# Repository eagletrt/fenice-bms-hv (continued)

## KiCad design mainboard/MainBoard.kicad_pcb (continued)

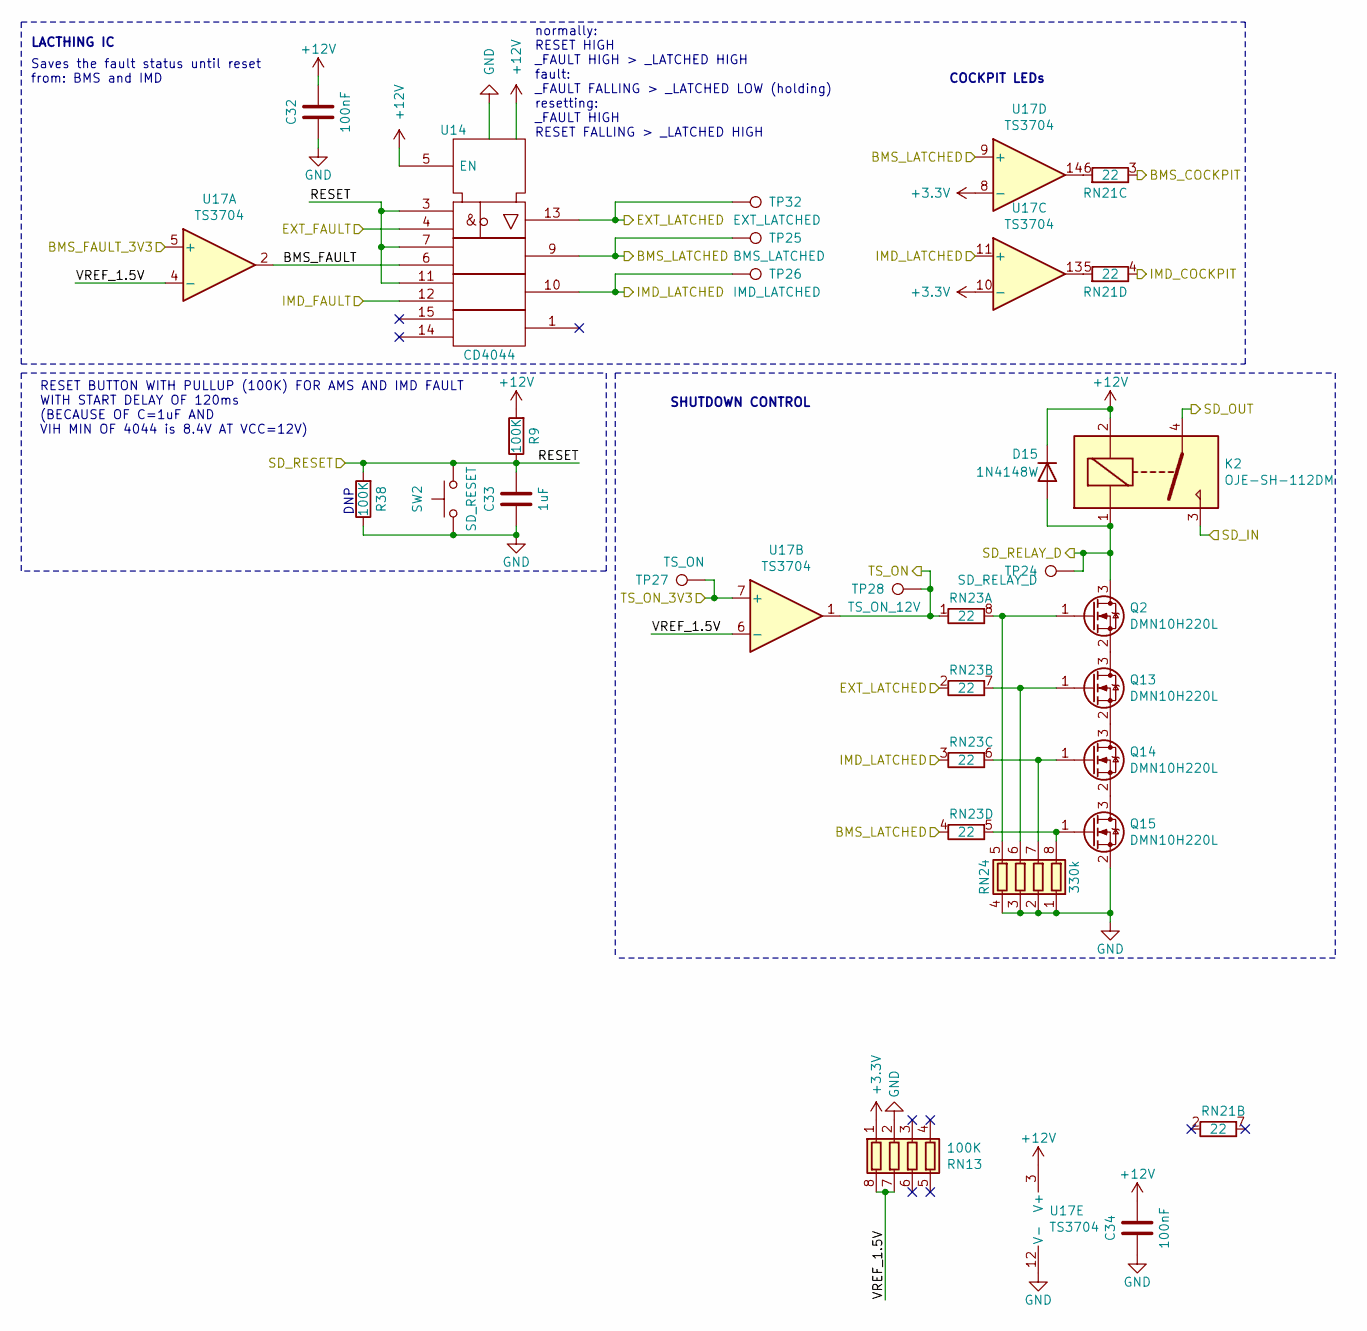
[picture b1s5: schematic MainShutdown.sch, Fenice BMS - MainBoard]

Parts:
C32, C34: 100nF; C_0603_1608Metric
C33: 1uF; C_0805_2012Metric
D15: 1N4148W; D_SOD-123
K2: OJE-SH-112DM
Q2, Q13, Q14, Q15: DMN10H220L; SOT-23
R9, R38: 100K; R_0603_1608Metric
RN13: 100K; R_Array_Convex_4x0603
RN21, RN23: 22; R_Array_Convex_4x0603
RN24: 330k; R_Array_Convex_4x0603
SW2: SD_RESET; SW_SPST_FSMSM
TP24: SD_RELAY_D; TestPoint_Pad_D1.0mm
TP25: BMS_LATCHED; TestPoint_Pad_D1.0mm
TP26: IMD_LATCHED; TestPoint_Pad_D1.0mm
TP27: TS_ON; TestPoint_Pad_D1.0mm
TP28: TS_ON_12V; TestPoint_Pad_D1.0mm
TP32: EXT_LATCHED; TestPoint_Pad_D1.0mm
U14: CD4044; TSSOP-16_4.4x5mm_P0.65mm
U17: TS3704; TSSOP-14_4.4x5mm_P0.65mm

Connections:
+12V: C32.1, C34.1, D15.1 (K), K2.2, R9.2, U14.5 (EN), U14.16 (Vdd), U17.3 (V+); also elsewhere on the board
/BMS_COCKPIT: RN21.3 (R3.1); also elsewhere on the board
/EXT_FAULT: U14.4; also elsewhere on the board
/IMD_COCKPIT: RN21.4 (R4.1); also elsewhere on the board
/IMD_FAULT: U14.12; also elsewhere on the board
/MCU/BMS_FAULT: U17.5 (+); also elsewhere on the board
/MCU/TS_ON: TP27.1, U17.7 (+); also elsewhere on the board
/Probing/BMS_LATCHED: RN23.4 (R4.1), TP25.1, U14.9, U17.9 (+); also elsewhere on the board
/Probing/EXT_LATCHED: RN23.2 (R2.1), TP32.1, U14.13; also elsewhere on the board
/Probing/IMD_LATCHED: RN23.3 (R3.1), TP26.1, U14.10, U17.11 (+); also elsewhere on the board
/Probing/SD_RELAY_D: D15.2 (A), K2.1, Q2.3 (D), TP24.1; also elsewhere on the board
/Probing/TS_ON: RN23.1 (R1.1), TP28.1, U17.1; also elsewhere on the board
/SD_IN: K2.3; also elsewhere on the board
/SD_OUT: K2.4; also elsewhere on the board
/SD_RESET: C33.1, R9.1, R38.2, SW2.1, U14.3, U14.7, U14.11; also elsewhere on the board
/Shutdown/BMS_FAULT: U14.6, U17.2
/Shutdown/VREF_1.5V: RN13.7 (R2.2), RN13.8 (R1.2), U17.4 (-), U17.6 (-)
GND: C32.2, C33.2, C34.2, Q15.2 (S), R38.1, RN13.2 (R2.1), RN24.1 (R1.1), RN24.2 (R2.1), RN24.3 (R3.1), RN24.4 (R4.1), SW2.2, U14.8 (Vss), U17.12 (V-); also elsewhere on the board
unnamed: Q2.1 (G), RN23.8 (R1.2), RN24.5 (R4.2)
unnamed: Q13.1 (G), RN23.7 (R2.2), RN24.6 (R3.2)
unnamed: Q13.2 (S), Q14.3 (D)
unnamed: Q2.2 (S), Q13.3 (D)
unnamed: Q14.1 (G), RN23.6 (R3.2), RN24.7 (R2.2)
unnamed: Q14.2 (S), Q15.3 (D)
unnamed: Q15.1 (G), RN23.5 (R4.2), RN24.8 (R1.2)
unnamed: RN21.5 (R4.2), U17.13
unnamed: RN21.6 (R3.2), U17.14

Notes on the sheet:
SHUTDOWN CONTROL
RESET BUTTON WITH PULLUP (100K) FOR AMS AND IMD FAULT WITH START DELAY OF 120ms (BECAUSE OF C=1uF AND VIH MIN OF 4044 is 8.4V AT VCC=12V)
LACTHING IC
Saves the fault status until reset from: BMS and IMD
normally: RESET HIGH _FAULT HIGH > _LATCHED HIGH fault: _FAULT FALLING > _LATCHED LOW (holding) resetting: _FAULT HIGH RESET FALLING > _LATCHED HIGH
DNP
COCKPIT LEDs

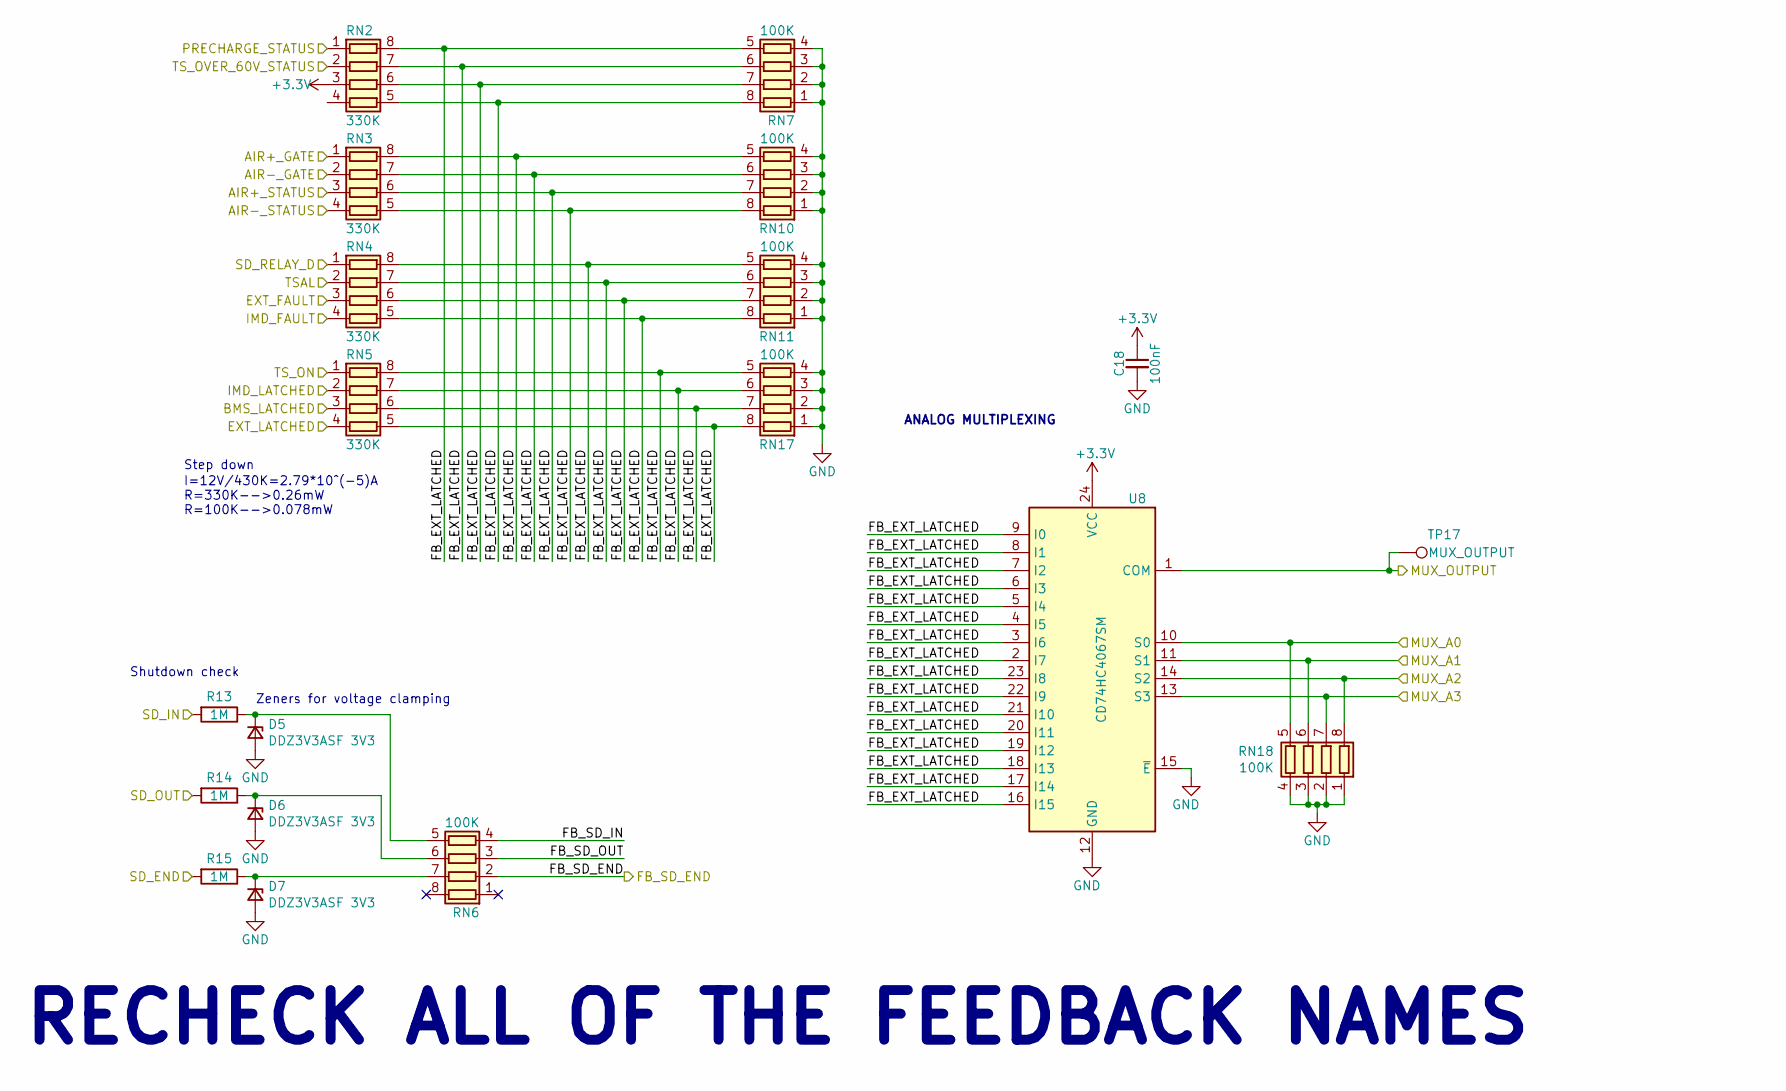
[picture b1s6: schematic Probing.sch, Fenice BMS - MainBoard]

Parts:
C18: 100nF; C_0603_1608Metric
D5, D6, D7: DDZ3V3ASF 3V3; D_SOD-323
R13, R14, R15: 1M; R_0603_1608Metric
RN2, RN3, RN4, RN5: 330K; R_Array_Convex_4x0603
RN6, RN7, RN10, RN11, RN17, RN18: 100K; R_Array_Convex_4x0603
TP17: MUX_OUTPUT; TestPoint_Pad_D1.0mm
U8: CD74HC4067SM; TSSOP-24_4.4x7.8mm_P0.65mm

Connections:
/AIRs/AIR+_GATE: RN3.1 (R1.1); also elsewhere on the board
/AIRs/AIR+_STATUS: RN3.3 (R3.1); also elsewhere on the board
/AIRs/AIR-_GATE: RN3.2 (R2.1); also elsewhere on the board
/AIRs/AIR-_STATUS: RN3.4 (R4.1); also elsewhere on the board
/EXT_FAULT: RN4.3 (R3.1); also elsewhere on the board
/HV/PRECHARGE_STATUS: RN2.1 (R1.1); also elsewhere on the board
/HV/TS_OVER_60V_STATUS: RN2.2 (R2.1); also elsewhere on the board
/IMD_FAULT: RN4.4 (R4.1); also elsewhere on the board
/MCU/FB_SD_END: RN6.2 (R2.1); also elsewhere on the board
/MCU/MUX_A0: RN18.5 (R4.2), U8.10 (S0)
/MCU/MUX_A1: RN18.6 (R3.2), U8.11 (S1)
/MCU/MUX_A2: RN18.8 (R1.2), U8.14 (S2)
/MCU/MUX_A3: RN18.7 (R2.2), U8.13 (S3)
/MCU/MUX_OUTPUT: TP17.1, U8.1 (COM); also elsewhere on the board
/Probing/BMS_LATCHED: RN5.3 (R3.1); also elsewhere on the board
/Probing/EXT_LATCHED: RN5.4 (R4.1); also elsewhere on the board
/Probing/FB_EXT_LATCHED: RN2.5 (R4.2), RN2.6 (R3.2), RN2.7 (R2.2), RN2.8 (R1.2), RN3.5 (R4.2), RN3.6 (R3.2), RN3.7 (R2.2), RN3.8 (R1.2), RN4.5 (R4.2), RN4.6 (R3.2), RN4.7 (R2.2), RN4.8 (R1.2), RN5.5 (R4.2), RN5.6 (R3.2), RN5.7 (R2.2), RN5.8 (R1.2), RN7.5 (R4.2), RN7.6 (R3.2), RN7.7 (R2.2), RN7.8 (R1.2), RN10.5 (R4.2), RN10.6 (R3.2), RN10.7 (R2.2), RN10.8 (R1.2), RN11.5 (R4.2), RN11.6 (R3.2), RN11.7 (R2.2), RN11.8 (R1.2), RN17.5 (R4.2), RN17.6 (R3.2), RN17.7 (R2.2), RN17.8 (R1.2), U8.2 (I7), U8.3 (I6), U8.4 (I5), U8.5 (I4), U8.6 (I3), U8.7 (I2), U8.8 (I1), U8.9 (I0), U8.16 (I15), U8.17 (I14), U8.18 (I13), U8.19 (I12), U8.20 (I11), U8.21 (I10), U8.22 (I9), U8.23 (I8)
/Probing/FB_SD_IN: RN6.4 (R4.1)
/Probing/FB_SD_OUT: RN6.3 (R3.1)
/Probing/IMD_LATCHED: RN5.2 (R2.1); also elsewhere on the board
/Probing/SD_RELAY_D: RN4.1 (R1.1); also elsewhere on the board
/Probing/TS_ON: RN5.1 (R1.1); also elsewhere on the board
/SD_END: R15.2; also elsewhere on the board
/SD_IN: R13.2; also elsewhere on the board
/SD_OUT: R14.2; also elsewhere on the board
/TSAL: RN4.2 (R2.1); also elsewhere on the board
GND: C18.2, D5.2 (A), D6.2 (A), D7.2 (A), RN7.1 (R1.1), RN7.2 (R2.1), RN7.3 (R3.1), RN7.4 (R4.1), RN10.1 (R1.1), RN10.2 (R2.1), RN10.3 (R3.1), RN10.4 (R4.1), RN11.1 (R1.1), RN11.2 (R2.1), RN11.3 (R3.1), RN11.4 (R4.1), RN17.1 (R1.1), RN17.2 (R2.1), RN17.3 (R3.1), RN17.4 (R4.1), RN18.1 (R1.1), RN18.2 (R2.1), RN18.3 (R3.1), RN18.4 (R4.1), U8.12 (GND), U8.15 (~E); also elsewhere on the board
unnamed: D5.1 (K), R13.1, RN6.5 (R4.2)
unnamed: D6.1 (K), R14.1, RN6.6 (R3.2)
unnamed: D7.1 (K), R15.1, RN6.7 (R2.2)

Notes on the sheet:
I=12V/430K=2.79*10^(-5)A R=330K-->0.26mW R=100K-->0.078mW
Step down
Zeners for voltage clamping
ANALOG MULTIPLEXING
RECHECK ALL OF THE FEEDBACK NAMES
Shutdown check

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
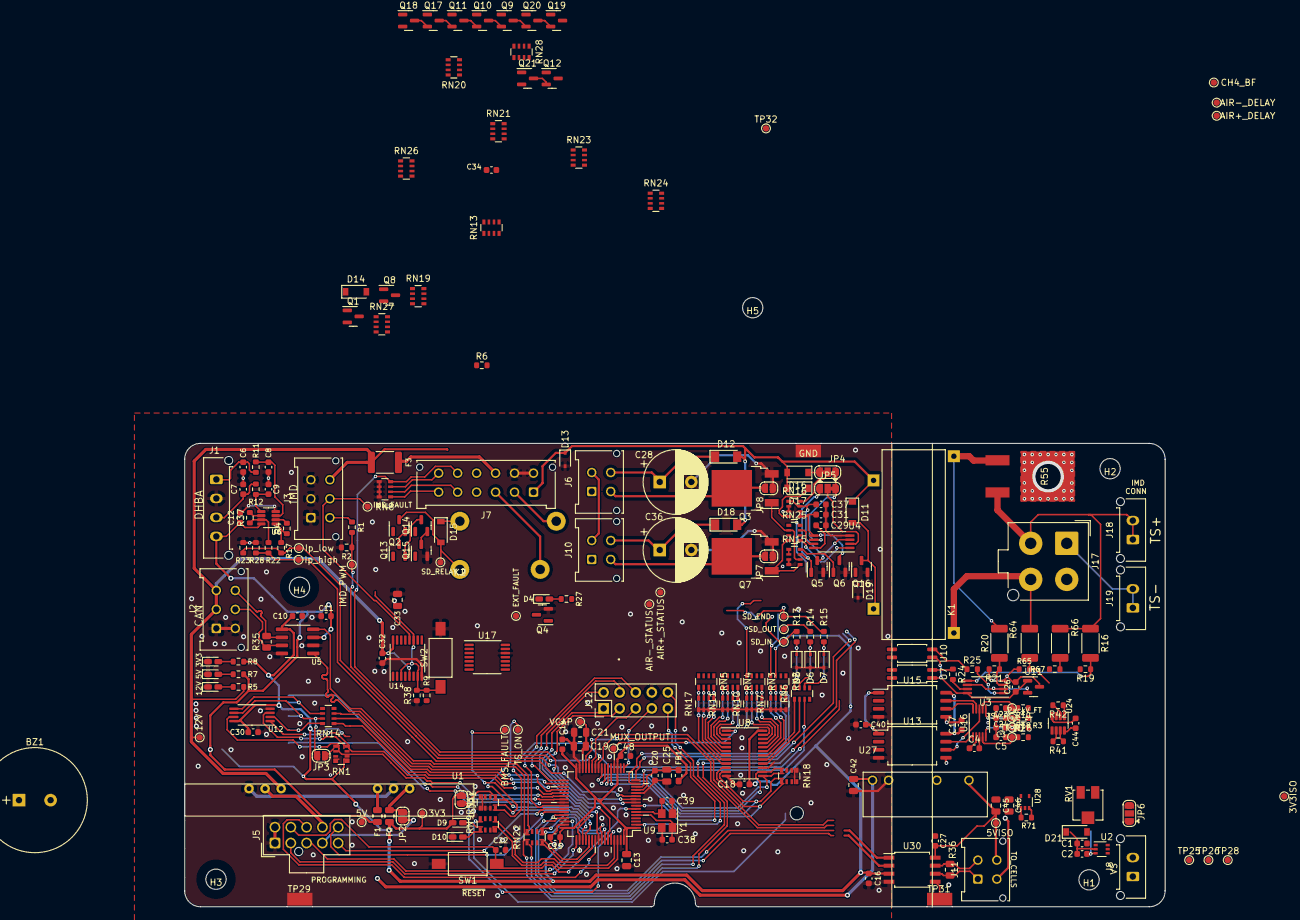
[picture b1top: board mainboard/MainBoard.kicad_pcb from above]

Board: 2 copper layers, 155.0 x 73.2 mm, 246 parts (1 on the bottom side), 199 nets.

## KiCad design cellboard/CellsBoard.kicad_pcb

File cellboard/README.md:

# CELLBOARD
Formula SAE - unitn

## Authors
Latest first:  
- Francesco Osti v2.1.4  
- Franco Tabarelli v2.0 - 2.1.3  
- Gregor Gombač v0 -   

## Version 2.1.4
Compared to last version we now use NTC termistor to monitor temperature and no longer use digital temperature sensors mounted on flexible PCB

## Project structure
```
cellboard
|-- CellsBoard.pro                    # Project file
|-- CellsBoard.sch                    # Cellboard main schematic
|-- PowerSupply.sch                   # Power sources schematic
|-- Balance.sch                       # Balancer schematic
|-- temperatureADC.sch                # Temperature measurement schematic
|-- Temperature section.sch           # STM microcontroller schematic
|-- LTC6813-1.sch                     # Cell voltage monitor IC schematic
|-- CellsBoard.kicad_pcb              # PCB
|-- CellsBoard-cache.lib              # Local cache of symbols        
|-- CellsBoard.net                    # Netlist
|-- CellsBoard-rescue.dcm             # Component library stuff
|-- CellsBoard-rescue.lib             # Component library stuff
|-- fp-info-cache                     # Cache of footprints
|-- fp-lib-table                      # List of footprint lib files
|-- sym-lib-table                     # List of symbols lib files
|-- modules/                          # Local symbol library files
|   |-- CellsBoard.pretty/            # Local footprint library files
|   |-- logo.kicad_mod/               # Logos fotprints
|   |-- packages3d/                   # 3D models
|   |-- simbolo_E-Agle.pretty/        # Logos E-Agle fotprints
|   |-- simbolo HV/                   # Logos HV fotprints
|-- gerber/                           # Gerber outputs
|-- library/                          # Local symbol library files
```

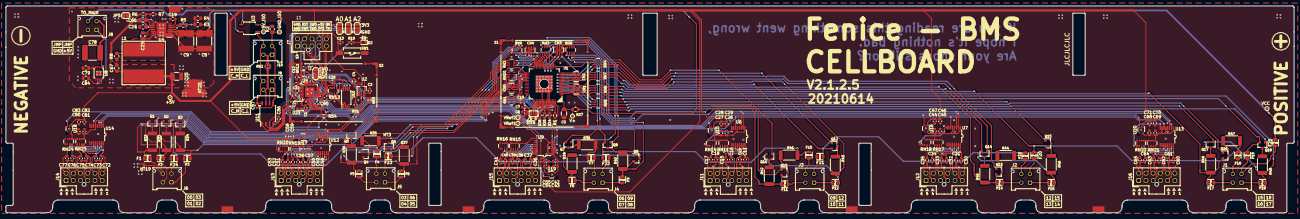
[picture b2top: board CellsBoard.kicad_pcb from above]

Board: 2 copper layers, 445.5 x 71.5 mm, 275 parts (0 on the bottom side), 245 nets.

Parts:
C1, C11, C13, C14, C15, C16, C17, C18, C20, C21, C22, C26, C28, C30, C31, C32, C33, C34, C35, C36, C37, C38, C39, C40, C41, C42, C45, C47, C48, C49, C50, C51, C52, C53, C54, C57, C59, C60, C61, C62, C63, C64, C65, C69, C71, C72, C73, C74, C75, C76, C77, C81, C83, C85, C86, C87: 100nF; C_0603_1608Metric
C2, C3, C4, C6, C7, C10, C12, C27, C29, C43, C44, C46, C55, C56, C58, C68, C70, C80, C82: 1uF; C_0603_1608Metric
C5: 100nF_HV; C_1206_3216Metric
C8, C9, C78: 1u_HV; C_2220_5650Metric_Pad1.97x5.40mm_HandSolder
C19: 22n; C_0603_1608Metric_Pad1.08x0.95mm_HandSolder
C23, C66: 10n; C_0805_2012Metric_Pad1.18x1.45mm_HandSolder
C24: 1u; C_0805_2012Metric_Pad1.18x1.45mm_HandSolder
C25: 47u; C_1210_3225Metric_Pad1.33x2.70mm_HandSolder
C67: 3n; C_0805_2012Metric_Pad1.18x1.45mm_HandSolder
C79: 100n; C_0805_2012Metric
C84: 10n; C_0805_2012Metric
CN1, CN2, CN3, CN4, CN5: 10nF_array; C_4Array_1206
D2: LED_Small; D_0603_1608Metric
F1, F2, F3, F4, F5, F6, F7, F8, F9, F10, F11, F12, F13, F14, F15, F16, F17, F18, F19, F20, F21, F22, F23, F24, F25: Fuse; Fuse_0805
J1, J2, J3, J4, J5, J6: Conn_02x02_Odd_Even; Molex_Micro-Fit_3.0_43045-0412_2x02_P3.00mm_Vertical
J7: Conn_02x05_Top_Bottom; Molex_Nano-Fit_105310-xx10_2x05_P2.50mm_Vertical
J8: Conn_02x02_Counter_Clockwise; Molex_Micro-Fit_3.0_43045-0412_2x02_P3.00mm_Vertical
J9, J10: BUS; Molex_Micro-Fit_3.0_43045-0412_2x02_P3.00mm_Vertical
J11, J12, J13, J14, J15, J16: Conn_02x06_Top_Bottom; Molex_Nano-Fit_105310-xx12_2x06_P2.50mm_Vertical
JP1, JP2, JP3, JP4: SolderJumper_3_Open; SolderJumper-3_P1.3mm_Open_RoundedPad1.0x1.5mm
JP5: SolderJumper_2_Open; SolderJumper-2_P1.3mm_Open_RoundedPad1.0x1.5mm
JP20: DTEN; Jumper_adafruit
L1: 56u; sdr1307
NT0, NT1, NT2, NT3, NT4, NT5, NT6, NT7, NT8, NT9, NT10, NT11, NT12, NT13, NT14, NT15, NT16, NT17, NT18, NT19: Net-Tie_2; NetTie-2_SMD_Pad0.5mm
NT20: Net-Tie_2; NetTie-2_SMD_Pad2.0mm
Q1, Q2, Q3, Q4, Q5, Q6, Q7, Q8, Q9, Q10, Q11, Q12, Q13, Q14: TSM3401CX RFG; SOT-23
Q15, Q16, Q17, Q18: BSS308PE; SOT-23
R1: 100; R_0603_1608Metric
R2: 1.24k; R_0805_2012Metric_Pad1.20x1.40mm_HandSolder
R3: 100k; R_0805_2012Metric_Pad1.20x1.40mm_HandSolder
R4: 2k; R_0805_2012Metric_Pad1.20x1.40mm_HandSolder
R5: 215k; R_0805_2012Metric_Pad1.20x1.40mm_HandSolder
R6: 3k; R_0603_1608Metric_Pad0.98x0.95mm_HandSolder
R7: 2k; R_0603_1608Metric_Pad0.98x0.95mm_HandSolder
R8: 255k; R_0805_2012Metric_Pad1.20x1.40mm_HandSolder
R19: 3K3; R_0603_1608Metric
R24, R25: 1k; R_0603_1608Metric
R26: 1M; R_0603_1608Metric
R27: 100; R_0805_2012Metric
R32, R33, R34, R35, R36, R37, R38, R39, R40, R41, R42, R43, R44, R45, R46, R47, R48, R49: Rdsc; R_2512_6332Metric
R51: 1K; R_0603_1608Metric
R52: 150; R_0603_1608Metric
R53: 5K; R_0603_1608Metric
R54: 10K; R_0603_1608Metric
RN1, RN2, RN3, RN4, RN5: 3K3; R_Array_Convex_4x0603
RN6, RN7, RN8, RN9, RN10: 39; R_Array_Convex_4x0603
RN11, RN14, RN15, RN16, RN17, RN18, RN19, RN20, RN21, RN22, RN23, RN24: x; R_Array_Convex_4x0603
RN12: 1K; R_Array_Convex_2x0603
RN13: 1K; R_Array_Convex_4x0603
S1: RF_Shield_One_Piece; Harwin_shield_30x30mm_right_angle_clips
S2: RF_Shield_One_Piece; Harwin_shield_20x30mm_only_right_angle_clips
SW1: RESET; Button_SMD_6x3.5x4.3mm
TP1, TP2, TP3, TP4, TP7: TestPoint; TestPoint_GNDedge_toponly
TP5: VRef1; TestPoint_Pad_D1.0mm
TP6: VRef2; TestPoint_Pad_D1.0mm
TP8: V+; TestPoint_Pad_D1.0mm
TP9: +5V; TestPoint_Pad_D1.0mm
TP10: 5V_ISO; TestPoint_Pad_D1.0mm
TP11: GND_ISO; TestPoint_Pad_D1.0mm
TP12: VCC; TestPoint_Pad_D1.0mm
U1: LTC6813-1; LTC6813-1_minimal
U2: MCP1812; SOT-23_Handsoldering
U3: CPC1125N; SOP-4_3.8x4.1mm_P2.54mm
U4: LM5161PWP; HTSSOP-14-1EP_4.4x5mm_P0.65mm_EP3.4x5mm_Mask3x3.1mm
U5: STM32L432KBUx; QFN-32-1EP_5x5mm_P0.5mm_EP3.45x3.45mm
U6, U7, U9, U12, U13, U14: ADC128D818; TSSOP-16_4.4x5mm_P0.65mm
U8: MAQ5281; MSOP-8-1EP_3x3mm_P0.65mm_EP1.68x1.88mm
U10: M95256-W; TSSOP-8_4.4x3mm_P0.65mm
U11: MAX14878AWA+; SOIC-8_5.23x5.23mm_P1.27mm
U15, U16, U17, U18, U19, U20: MCP1811AT-033LT; SOT-353_SC-70-5
U21: DSC61XX; 4-Lead_CDFN_2.5x2.0mm

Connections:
+3V3: C1.2, C2.1, C4.1, C12.1, C20.2, C21.1, C22.1, C85.1, C86.2, J7.4, JP1.3, JP3.3, JP4.3, R51.2, R53.1, R54.2, RN12.1, RN12.2, RN13.2, RN13.3, RN13.4, U2.1, U5.1, U5.5, U5.17, U10.8, U11.3, U21.1, U21.4
+5V: C3.1, C10.1, C25.2, C28.2, C29.2, C46.2, C47.2, C54.2, C55.2, C58.2, C59.2, C67.2, C70.2, C71.2, C82.2, C83.2, J7.9, JP20.1, L1.2, R6.1, R26.2, TP9.1, U1.48, U2.2, U15.1, U16.1, U17.1, U18.1, U19.1, U20.1
/BATTERY MANAGER/C0: CN5.3, CN5.7, RN10.6, U1.38
/BATTERY MANAGER/C1: CN5.4, CN5.6, RN10.7, U1.36
/BATTERY MANAGER/C2: CN4.1, CN5.5, RN10.8, U1.34
/BATTERY MANAGER/C3: CN4.2, CN4.8, RN9.5, U1.32
/BATTERY MANAGER/C4: CN4.3, CN4.7, RN9.6, U1.30
/BATTERY MANAGER/C5: CN4.4, CN4.6, RN9.7, U1.28
/BATTERY MANAGER/C6: CN3.1, CN4.5, RN9.8, U1.26
/BATTERY MANAGER/C7: CN3.2, CN3.8, RN8.5, U1.24
/BATTERY MANAGER/C8: CN3.3, CN3.7, RN8.6, U1.22
/BATTERY MANAGER/C9: CN3.4, CN3.6, RN8.7, U1.20
/BATTERY MANAGER/C10: CN2.1, CN3.5, RN8.8, U1.18
/BATTERY MANAGER/C11: CN2.2, CN2.8, RN7.5, U1.16
/BATTERY MANAGER/C12: CN2.3, CN2.7, RN7.6, U1.14
/BATTERY MANAGER/C13: CN2.4, CN2.6, RN7.7, U1.12
/BATTERY MANAGER/C14: CN1.1, CN2.5, RN7.8, U1.10
/BATTERY MANAGER/C15: CN1.2, CN1.8, RN6.5, U1.8
/BATTERY MANAGER/C16: CN1.3, CN1.7, RN6.6, U1.6
/BATTERY MANAGER/C17: CN1.4, CN1.6, RN6.7, U1.4
/BATTERY MANAGER/C18: CN1.5, RN6.8, U1.2
/BATTERY MANAGER/CB0: NT0.2, RN10.3
/BATTERY MANAGER/CB1: NT1.2, RN10.2
/BATTERY MANAGER/CB2: NT2.2, RN10.1
/BATTERY MANAGER/CB3: NT3.2, RN9.4
/BATTERY MANAGER/CB4: NT4.2, RN9.3
/BATTERY MANAGER/CB5: NT5.2, RN9.2
/BATTERY MANAGER/CB6: NT6.2, RN9.1
/BATTERY MANAGER/CB7: NT7.2, RN8.4
/BATTERY MANAGER/CB8: NT8.2, RN8.3
/BATTERY MANAGER/CB9: NT9.2, RN8.2
/BATTERY MANAGER/CB10: NT10.2, RN8.1
/BATTERY MANAGER/CB11: NT11.2, RN7.4
/BATTERY MANAGER/CB12: NT12.2, RN7.3
/BATTERY MANAGER/CB13: NT13.2, RN7.2
/BATTERY MANAGER/CB14: NT14.2, RN7.1
/BATTERY MANAGER/CB15: NT15.2, RN6.4
/BATTERY MANAGER/CB16: NT16.2, RN6.3
/BATTERY MANAGER/CB17: NT17.2, RN6.2
/BATTERY MANAGER/CB18: NT18.2, RN6.1
/BATTERY MANAGER/CLK: U1.62, U5.11
/BATTERY MANAGER/IBIAS: R25.1, U1.57
/BATTERY MANAGER/ICMP: R24.2, R25.2, U1.58
/BATTERY MANAGER/MISO: R53.2, U1.54, U5.12
/BATTERY MANAGER/MOSI: U1.53, U5.13
/BATTERY MANAGER/V+: C5.1, R27.1, TP8.1, U1.1
/BATTERY MANAGER/VRef1: C6.1, TP5.1, U1.51
/BATTERY MANAGER/VRef2: C7.1, TP6.1, U1.50
/BATTERY MANAGER/WDT: R26.1, U1.56
/CB0: F1.2, NT0.1, R32.1
/CB0N: F1.1, J6.4, NT19.1
/CB1: F2.2, NT1.1, Q1.2, R33.1
/CB1N: F2.1, J6.2
/CB2: F3.2, NT2.1, Q2.2, R34.1
/CB2N: F3.1, J6.1
/CB3: F4.2, F24.2, NT3.1, Q3.2, R35.1
/CB3N-1: F4.1, J5.4
/CB3N-2: F24.1, J6.3
/CB4: F5.2, NT4.1, Q4.2, R36.1
/CB4N: F5.1, J5.2
/CB5: F6.2, NT5.1, Q5.2, R37.1
/CB5N: F6.1, J5.1
/CB6: F7.2, F23.2, NT6.1, Q6.2, R38.1
/CB6N-1: F7.1, J4.4
/CB6N-2: F23.1, J5.3
/CB7: F8.2, NT7.1, Q7.2, R39.1
/CB7N: F8.1, J4.2
/CB8: F9.2, NT8.1, Q8.2, R40.1
/CB8N: F9.1, J4.1
/CB9: F10.2, F22.2, NT9.1, Q9.2, R41.1
/CB9N-1: F22.1, J4.3
/CB9N-2: F10.1, J3.4
/CB10: F11.2, NT10.1, Q10.2, R42.1
/CB10N: F11.1, J3.2
/CB11: F12.2, NT11.1, Q11.2, R43.1
/CB11N: F12.1, J3.1
/CB12: F13.2, F21.2, NT12.1, Q12.2, R44.1
/CB12N-1: F13.1, J2.4
/CB12N-2: F21.1, J3.3
/CB13: F14.2, NT13.1, Q13.2, R45.1
/CB13N: F14.1, J2.2
/CB14: F15.2, NT14.1, Q14.2, R46.1
/CB14N: F15.1, J2.1
/CB15: F16.2, F20.2, NT15.1, Q15.2, R47.1
/CB15N-1: F16.1, J1.4
/CB15N-2: F20.1, J2.3
/CB16: F17.2, NT16.1, Q16.2, R48.1
/CB16N: F17.1, J1.2
/CB17: F18.2, NT17.1, Q17.2, R49.1
/CB17N: F18.1, J1.1
/CB18: F19.2, NT18.1, Q18.2
/CB18N: F19.1, F25.1, J1.3
/DCDC_80Vto5V/5V_ISO: C87.2, J9.4, J10.4, TP10.1, U3.1, U11.8
/DCDC_80Vto5V/120V_linreg: C78.2, J8.3, U8.1
/DCDC_80Vto5V/EN-D: R3.1, R4.2, U4.4
/DCDC_80Vto5V/EN-DCDC1: R3.2, U3.4
/DCDC_80Vto5V/FB-D: C66.1, R6.2, R7.1, U4.9
/DCDC_80Vto5V/GND_ISO: C87.1, J9.3, J10.3, R2.2, TP11.1, U11.5
/DCDC_80Vto5V/GND_SUPPLY: C8.1, C9.1, C19.1, C24.1, C25.1, C78.1, C79.2, C84.2, J8.2, NT20.1, R4.1, R7.2, TP7.1, U4.1, U4.2, U4.15, U8.5, U8.9
/DCDC_80Vto5V/SS-D: C19.2, U4.6
/DCDC_80Vto5V/SW-D: C23.1, L1.1, R8.2, U4.12, U4.13, U4.14
/DCDC_80Vto5V/VCC-D: C24.2, JP5.2, U4.10
/MOS_Balancer_Passive_metod/DIS_1: Q1.3, R32.2
/MOS_Balancer_Passive_metod/DIS_2: Q2.3, R33.2
/MOS_Balancer_Passive_metod/DIS_3: Q3.3, R34.2
/MOS_Balancer_Passive_metod/DIS_4: Q4.3, R35.2
/MOS_Balancer_Passive_metod/DIS_5: Q5.3, R36.2
/MOS_Balancer_Passive_metod/DIS_6: Q6.3, R37.2
/MOS_Balancer_Passive_metod/DIS_7: Q7.3, R38.2
/MOS_Balancer_Passive_metod/DIS_8: Q8.3, R39.2
/MOS_Balancer_Passive_metod/DIS_9: Q9.3, R40.2
/MOS_Balancer_Passive_metod/DIS_10: Q10.3, R41.2
/MOS_Balancer_Passive_metod/DIS_11: Q11.3, R42.2
/MOS_Balancer_Passive_metod/DIS_12: Q12.3, R43.2
/MOS_Balancer_Passive_metod/DIS_13: Q13.3, R44.2
/MOS_Balancer_Passive_metod/DIS_14: Q14.3, R45.2
/MOS_Balancer_Passive_metod/DIS_15: Q15.3, R46.2
/MOS_Balancer_Passive_metod/DIS_16: Q16.3, R47.2
/MOS_Balancer_Passive_metod/DIS_17: Q17.3, R48.2
/MOS_Balancer_Passive_metod/DIS_18: Q18.3, R49.2
/MOS_Balancer_Passive_metod/Q_S1: Q1.1, RN1.6
/MOS_Balancer_Passive_metod/Q_S2: Q2.1, RN1.5
/MOS_Balancer_Passive_metod/Q_S3: Q3.1, RN2.8
/MOS_Balancer_Passive_metod/Q_S4: Q4.1, RN2.7
/MOS_Balancer_Passive_metod/Q_S5: Q5.1, RN2.6
/MOS_Balancer_Passive_metod/Q_S6: Q6.1, RN2.5
/MOS_Balancer_Passive_metod/Q_S7: Q7.1, RN3.8
/MOS_Balancer_Passive_metod/Q_S8: Q8.1, RN3.7
/MOS_Balancer_Passive_metod/Q_S9: Q9.1, RN3.6
/MOS_Balancer_Passive_metod/Q_S10: Q10.1, RN3.5
/MOS_Balancer_Passive_metod/Q_S11: Q11.1, RN4.8
/MOS_Balancer_Passive_metod/Q_S12: Q12.1, RN4.7
/MOS_Balancer_Passive_metod/Q_S13: Q13.1, RN4.6
/MOS_Balancer_Passive_metod/Q_S14: Q14.1, RN4.5
/MOS_Balancer_Passive_metod/Q_S15: Q15.1, RN5.8
/MOS_Balancer_Passive_metod/Q_S16: Q16.1, RN5.7
/MOS_Balancer_Passive_metod/Q_S17: Q17.1, RN5.6
/MOS_Balancer_Passive_metod/Q_S18: Q18.1, RN5.5
/S1: RN1.3, U1.37
/S2: RN1.4, U1.35
/S3: RN2.1, U1.33
/S4: RN2.2, U1.31
/S5: RN2.3, U1.29
/S6: RN2.4, U1.27
/S7: RN3.1, U1.25
/S8: RN3.2, U1.23
/S9: RN3.3, U1.21
/S10: RN3.4, U1.19
/S11: RN4.1, U1.17
/S12: RN4.2, U1.15
/S13: RN4.3, U1.13
/S14: RN4.4, U1.11
/S15: RN5.1, U1.9
/S16: RN5.2, U1.7
/S17: RN5.3, U1.5
/S18: RN5.4, U1.3
/STM/ADC_nINT: R54.1, U5.18, U6.6, U7.6, U9.6, U12.6, U13.6, U14.6
/STM/ADD_0: JP1.2, U5.9
/STM/ADD_1: JP3.2, U5.8
/STM/ADD_2: JP4.2, U5.7
/STM/CANH_ISO: J9.2, J10.2, R52.1, U11.7
/STM/CANL_ISO: J9.1, J10.1, R52.2, U11.6
/STM/CAN_RX: U5.21, U11.1
/STM/CAN_TX: U5.22, U11.2
/STM/CS_EEPROM: RN13.5, U5.10, U10.1
/STM/MISO_EEPROM: RN13.6, U5.27, U10.2
/STM/MOSI_EEPROM: U5.28, U10.5
/STM/POWER_SENS_1: U5.3, U15.3, U16.3, U20.3
/STM/POWER_SENS_2: U5.2, U17.3, U18.3, U19.3
/STM/RESET: C13.1, J7.7, SW1.2, U5.4
/STM/RX: J7.10, U5.20
/STM/SCK_EEPROM: JP2.1, RN13.8, U10.6
/STM/SCL: RN12.4, U5.29, U6.3, U7.3, U9.3, U12.3, U13.3, U14.3
/STM/SDA: RN12.3, U5.30, U6.2, U7.2, U9.2, U12.2, U13.2, U14.2
/STM/SPI_CS: U1.61, U5.14
/STM/SWCLK: J7.2, U5.24
/STM/SWDIO: J7.3, U5.23
/STM/SWO: J7.8, JP2.3
/STM/TX: J7.5, U5.19
/STM/temperatureADC_0/3V3_SENS: C80.2, C81.2, RN23.1, RN23.2, RN23.3, RN23.4, RN24.1, RN24.2, RN24.3, U14.1, U14.5, U18.5
/STM/temperatureADC_0/MID: RN24.5, RN24.6
/STM/temperatureADC_1/3V3_SENS: C56.2, C57.2, RN19.1, RN19.2, RN19.3, RN19.4, RN20.1, RN20.2, RN20.3, U12.1, U12.5, U17.5
/STM/temperatureADC_1/A0: RN20.5, RN20.6, U12.7
/STM/temperatureADC_2/3V3_SENS: C42.2, C43.2, RN15.1, RN15.2, RN15.3, RN15.4, RN16.1, RN16.2, RN16.3, U9.1, U9.5, U9.7, U19.5
/STM/temperatureADC_2/MID: RN16.5, RN16.6
/STM/temperatureADC_3/3V3_SENS: C26.2, C27.2, RN11.1, RN11.2, RN11.3, RN11.4, RN14.1, RN14.2, RN14.3, U6.1, U6.5, U15.5
/STM/temperatureADC_3/A1: RN14.5, RN14.6, U6.8
/STM/temperatureADC_4/3V3_SENS: C44.2, C45.2, RN17.1, RN17.2, RN17.3, RN17.4, RN18.1, RN18.2, RN18.3, U7.1, U7.5, U16.5
/STM/temperatureADC_4/A0: RN18.5, RN18.6, U7.7, U7.8
/STM/temperatureADC_5/3V3_SENS: C68.2, C69.2, RN21.1, RN21.2, RN21.3, RN21.4, RN22.1, RN22.2, RN22.3, U13.1, U13.5, U13.7, U20.5
/STM/temperatureADC_5/A1: RN22.5, RN22.6, U13.8
/STM/~HOLD~: RN13.7, U5.15, U10.7
/STM/~W~: R51.1, U10.3
GND: C1.1, C2.2, C3.2, C4.2, C5.2, C6.2, C7.2, C10.2, C11.2, C12.2, C13.2, C14.2, C15.2, C16.2, C17.2, C18.2, C20.1, C21.2, C22.2, C26.1, C27.1, C28.1, C29.1, C30.2, C31.2, C32.2, C33.2, C34.2, C35.2, C36.2, C37.2, C38.2, C39.2, C40.2, C41.2, C42.1, C43.1, C44.1, C45.1, C46.1, C47.1, C48.2, C49.2, C50.2, C51.2, C52.2, C53.2, C54.1, C55.1, C56.1, C57.1, C58.1, C59.1, C60.2, C61.2, C62.2, C63.2, C64.2, C65.2, C68.1, C69.1, C70.1, C71.1, C72.2, C73.2, C74.2, C75.2, C76.2, C77.2, C80.1, C81.1, C82.1, C83.1, C85.2, C86.1, CN5.1, CN5.2, CN5.8, D2.1, J7.1, J7.6, J11.1, J11.2, J11.3, J11.4, J11.5, J11.6, J12.1, J12.2, J12.3, J12.4, J12.5, J12.6, J13.1, J13.2, J13.3, J13.4, J13.5, J13.6, J14.1, J14.2, J14.3, J14.4, J14.5, J14.6, J15.1, J15.2, J15.3, J15.4, J15.5, J15.6, J16.1, J16.2, J16.3, J16.4, J16.5, J16.6, JP1.1, JP3.1, JP4.1, JP20.3, NT19.2, NT20.2, R24.1, RN10.4, RN10.5, RN13.1, RN14.4, RN16.4, RN18.4, RN20.4, RN22.4, RN24.4, S1.1, S2.1, SW1.1, TP1.1, TP2.1, TP3.1, TP4.1, U1.55, U1.59, U1.60, U1.65, U2.3, U5.16, U5.31, U5.32, U5.33, U6.4, U6.7, U7.4, U9.4, U9.8, U10.4, U11.4, U12.4, U12.8, U13.4, U14.4, U14.7, U14.8, U15.2, U16.2, U17.2, U18.2, U19.2, U20.2, U21.2
unnamed: C11.1, J11.12, RN11.8, U6.16
unnamed: C14.1, J11.11, RN11.7, U6.15
unnamed: C15.1, J11.10, RN11.6, U6.14
unnamed: C16.1, J11.9, RN11.5, U6.13
unnamed: C17.1, J11.8, RN14.8, U6.12
unnamed: C18.1, J11.7, RN14.7, U6.11
unnamed: C23.2, U4.11
unnamed: C30.1, J12.12, RN17.8, U7.16
unnamed: C31.1, J12.11, RN17.7, U7.15
unnamed: C32.1, J12.10, RN17.6, U7.14
unnamed: C33.1, J12.9, RN17.5, U7.13
unnamed: C34.1, J12.8, RN18.8, U7.12
unnamed: C35.1, J12.7, RN18.7, U7.11
unnamed: C36.1, J15.12, RN15.8, U9.16
unnamed: C37.1, J15.11, RN15.7, U9.15
unnamed: C38.1, J15.10, RN15.6, U9.14
unnamed: C39.1, J15.9, RN15.5, U9.13
unnamed: C40.1, J15.8, RN16.8, U9.12
unnamed: C41.1, J15.7, RN16.7, U9.11
unnamed: C48.1, J13.12, RN19.8, U12.16
unnamed: C49.1, J13.11, RN19.7, U12.15
unnamed: C50.1, J13.10, RN19.6, U12.14
unnamed: C51.1, J13.9, RN19.5, U12.13
unnamed: C52.1, J13.8, RN20.8, U12.12
unnamed: C53.1, J13.7, RN20.7, U12.11
unnamed: C60.1, J16.12, RN21.8, U13.16
unnamed: C61.1, J16.11, RN21.7, U13.15
unnamed: C62.1, J16.10, RN21.6, U13.14
unnamed: C63.1, J16.9, RN21.5, U13.13
unnamed: C64.1, J16.8, RN22.8, U13.12
unnamed: C65.1, J16.7, RN22.7, U13.11
unnamed: C66.2, C67.1, R8.1
unnamed: C72.1, J14.12, RN23.8, U14.16
unnamed: C73.1, J14.11, RN23.7, U14.15
unnamed: C74.1, J14.10, RN23.6, U14.14
unnamed: C75.1, J14.9, RN23.5, U14.13
unnamed: C76.1, J14.8, RN24.8, U14.12
unnamed: C77.1, J14.7, RN24.7, U14.11
unnamed: C79.1, U8.4
unnamed: C84.1, J8.1, U8.6, U8.8
unnamed: D2.2, R19.2
unnamed: JP2.2, U5.26
unnamed: JP5.1, U4.8
unnamed: JP20.2, U1.52
unnamed: R1.1, U1.63
unnamed: R1.2, U1.64
unnamed: R2.1, U3.2
unnamed: R5.2, U4.5
unnamed: R19.1, U5.25
unnamed: U5.6, U21.3
VCC: C8.2, C9.2, F25.2, J8.4, R5.1, R27.2, TP12.1, U3.3, U4.3

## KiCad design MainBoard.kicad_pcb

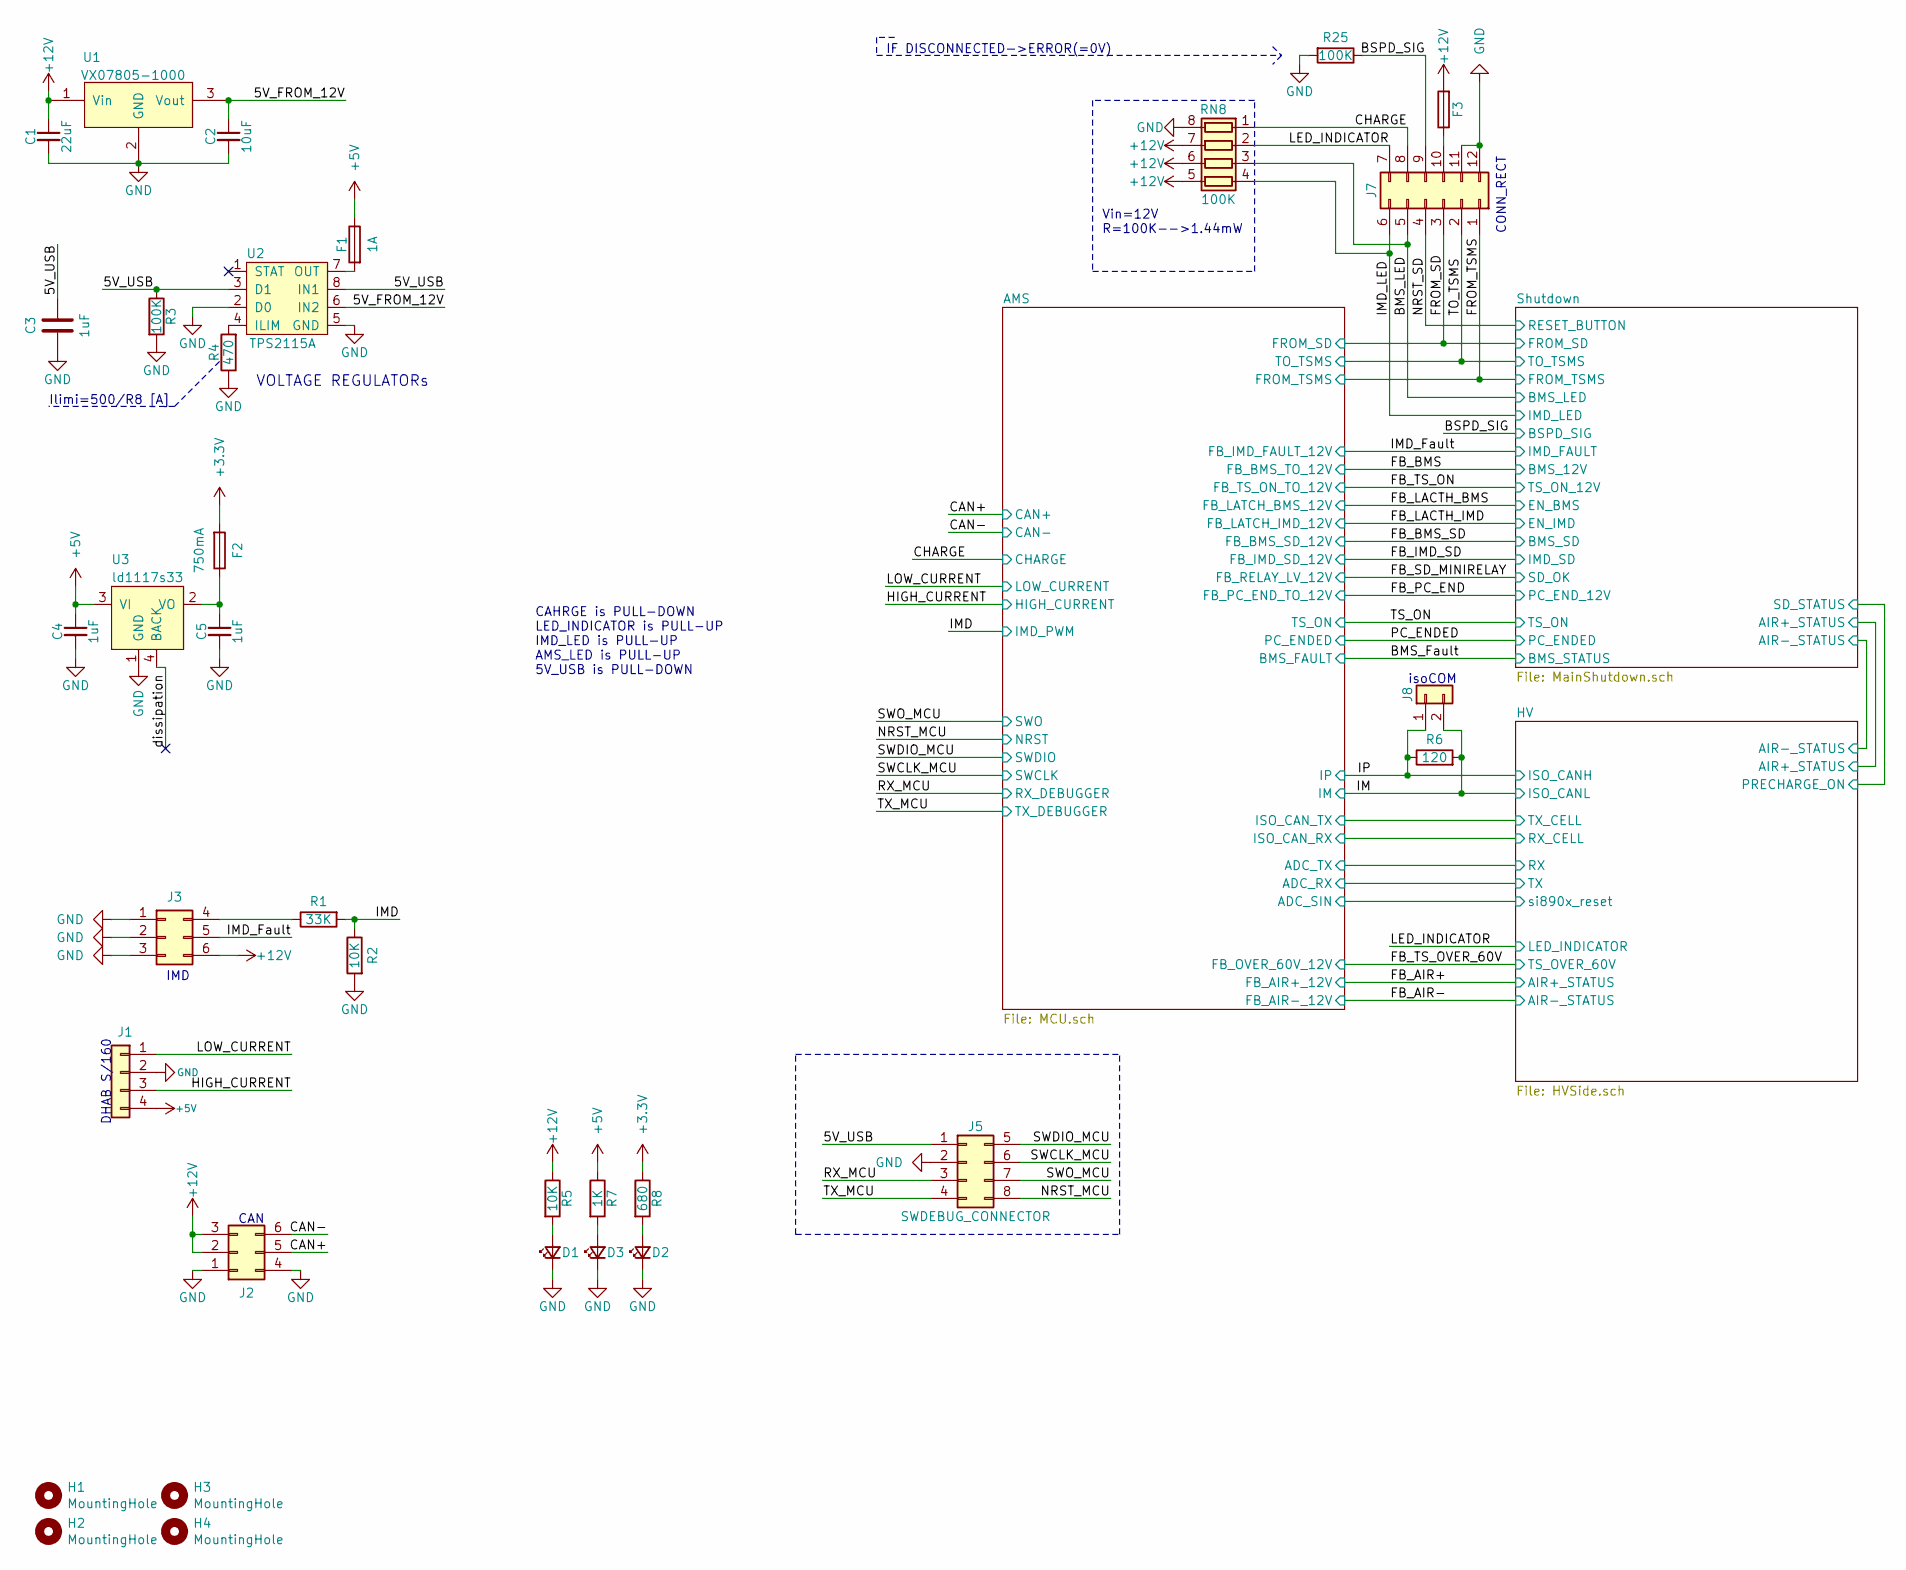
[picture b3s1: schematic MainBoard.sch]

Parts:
C1: 22uF; C_1206_3216Metric
C2: 10uF; C_0805_2012Metric
C3, C4, C5: 1uF; C_0805_2012Metric
D1, D2, D3: LED_Small; LED_0603_1608Metric_Castellated
F1: 1A; Fuse_0805_2012Metric
F2: 750mA; Fuse_0805_2012Metric
F3: 500mA; Fuse_1812_4532Metric
H1, H2, H3, H4: MountingHole; MountingHole_3mm
J1: CONN_1x4; Molex_Micro-Fit_3.0_43650-0415_1x04_P3.00mm_Vertical
J2, J3: CONN_2X3; Molex_Micro-Fit_3.0_43045-0612_2x03_P3.00mm_Vertical
J5: SWDEBUG_CONNECTOR; Molex_Nano-Fit_105310-xx08_2x04_P2.50mm_Vertical
J7: CONN_2X12; Molex_Micro-Fit_3.0_43045-1212_2x06_P3.00mm_Vertical
J8: CONN_1X2; Molex_Micro-Fit_3.0_43650-0215_1x02_P3.00mm_Vertical
R1: 33K; R_0603_1608Metric
R2, R5: 10K; R_0603_1608Metric
R3, R25: 100K; R_0603_1608Metric
R4: 470; R_0603_1608Metric
R6: 120; R_0805_2012Metric
R7: 1K; R_0603_1608Metric
R8: 680; R_0603_1608Metric
RN8: 100K; R_network_4x1_bourns_CAY16
U1: VX07805-1000; DC_DC_VXO7805_1000
U2: TPS2115A; TSSOP-8_4.4x3mm_P0.65mm
U3: ld1117s33; SOT-223

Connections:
+3V3: F2.2, R8.1; also elsewhere on the board
+5V: C4.1, F1.1, J1.4, R7.1, U3.3 (VI); also elsewhere on the board
+12V: C1.1, F3.2, J2.2, J2.3, J3.6, R5.1, RN8.5 (R4.2), RN8.6 (R3.2), RN8.7 (R2.2), U1.1 (Vin); also elsewhere on the board
/5V_FROM_12V: C2.1, U1.3 (Vout), U2.6 (IN2)
/5V_USB: C3.1, J5.1, R3.1, U2.3 (D1), U2.8 (IN1)
/BMS_LED: J7.5, RN8.3 (R3.1); also elsewhere on the board
/BSPD_SIG: J7.9, R25.1; also elsewhere on the board
/CAN+: J2.5; also elsewhere on the board
/CAN-: J2.6; also elsewhere on the board
/CHARGE: J7.8, RN8.1 (R1.1); also elsewhere on the board
/FROM_SD: J7.3; also elsewhere on the board
/FROM_TSMS: J7.1; also elsewhere on the board
/HIGH_CURRENT: J1.3; also elsewhere on the board
/IM: J8.2, R6.2; also elsewhere on the board
/IMD: R1.2, R2.1; also elsewhere on the board
/IMD_Fault: J3.5; also elsewhere on the board
/IMD_LED: J7.6, RN8.4 (R4.1); also elsewhere on the board
/IP: J8.1, R6.1; also elsewhere on the board
/LED_INDICATOR: J7.7, RN8.2 (R2.1); also elsewhere on the board
/LOW_CURRENT: J1.1; also elsewhere on the board
/NRST_MCU: J5.8; also elsewhere on the board
/NRST_SD: J7.4; also elsewhere on the board
/RX_MCU: J5.3; also elsewhere on the board
/SWCLK_MCU: J5.6; also elsewhere on the board
/SWDIO_MCU: J5.5; also elsewhere on the board
/SWO_MCU: J5.7; also elsewhere on the board
/TO_TSMS: J7.2; also elsewhere on the board
/TX_MCU: J5.4; also elsewhere on the board
/dissipation: U3.4 (BACK)
GND: C1.2, C2.2, C3.2, C4.2, C5.2, D1.1 (K), D2.1 (K), D3.1 (K), J1.2, J2.1, J2.4, J3.1, J3.2, J3.3, J5.2, J7.11, J7.12, R2.2, R3.2, R4.1, R25.2, RN8.8 (R1.2), U1.2 (GND), U2.2 (D0), U2.5 (GND), U3.1 (GND); also elsewhere on the board
unnamed: C5.1, F2.1, U3.2 (VO)
unnamed: D1.2 (A), R5.2
unnamed: D2.2 (A), R8.2
unnamed: D3.2 (A), R7.2
unnamed: F1.2, U2.7 (OUT)
unnamed: F3.1, J7.10
unnamed: J3.4, R1.1
unnamed: R4.2, U2.4 (ILIM)

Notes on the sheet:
Ilimi=500/R8 [A]
VOLTAGE REGULATORs
CAHRGE is PULL-DOWN LED_INDICATOR is PULL-UP IMD_LED is PULL-UP AMS_LED is PULL-UP 5V_USB is PULL-DOWN
DHAB S/160
CAN
IMD
CONN_RECT
isoCOM
Vin=12V R=100K-->1.44mW
IF DISCONNECTED->ERROR(=0V)
